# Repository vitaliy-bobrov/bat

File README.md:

# BAT

BAT - custom modified Rat circuit KiCad files.

The repository contains KiCad source files: schematic, PCB, BOM.

## Schematic

## PCB (3D preview)

## Interactive BOM

👉 [BOM](https://vitaliy-bobrov.github.io/bat/)

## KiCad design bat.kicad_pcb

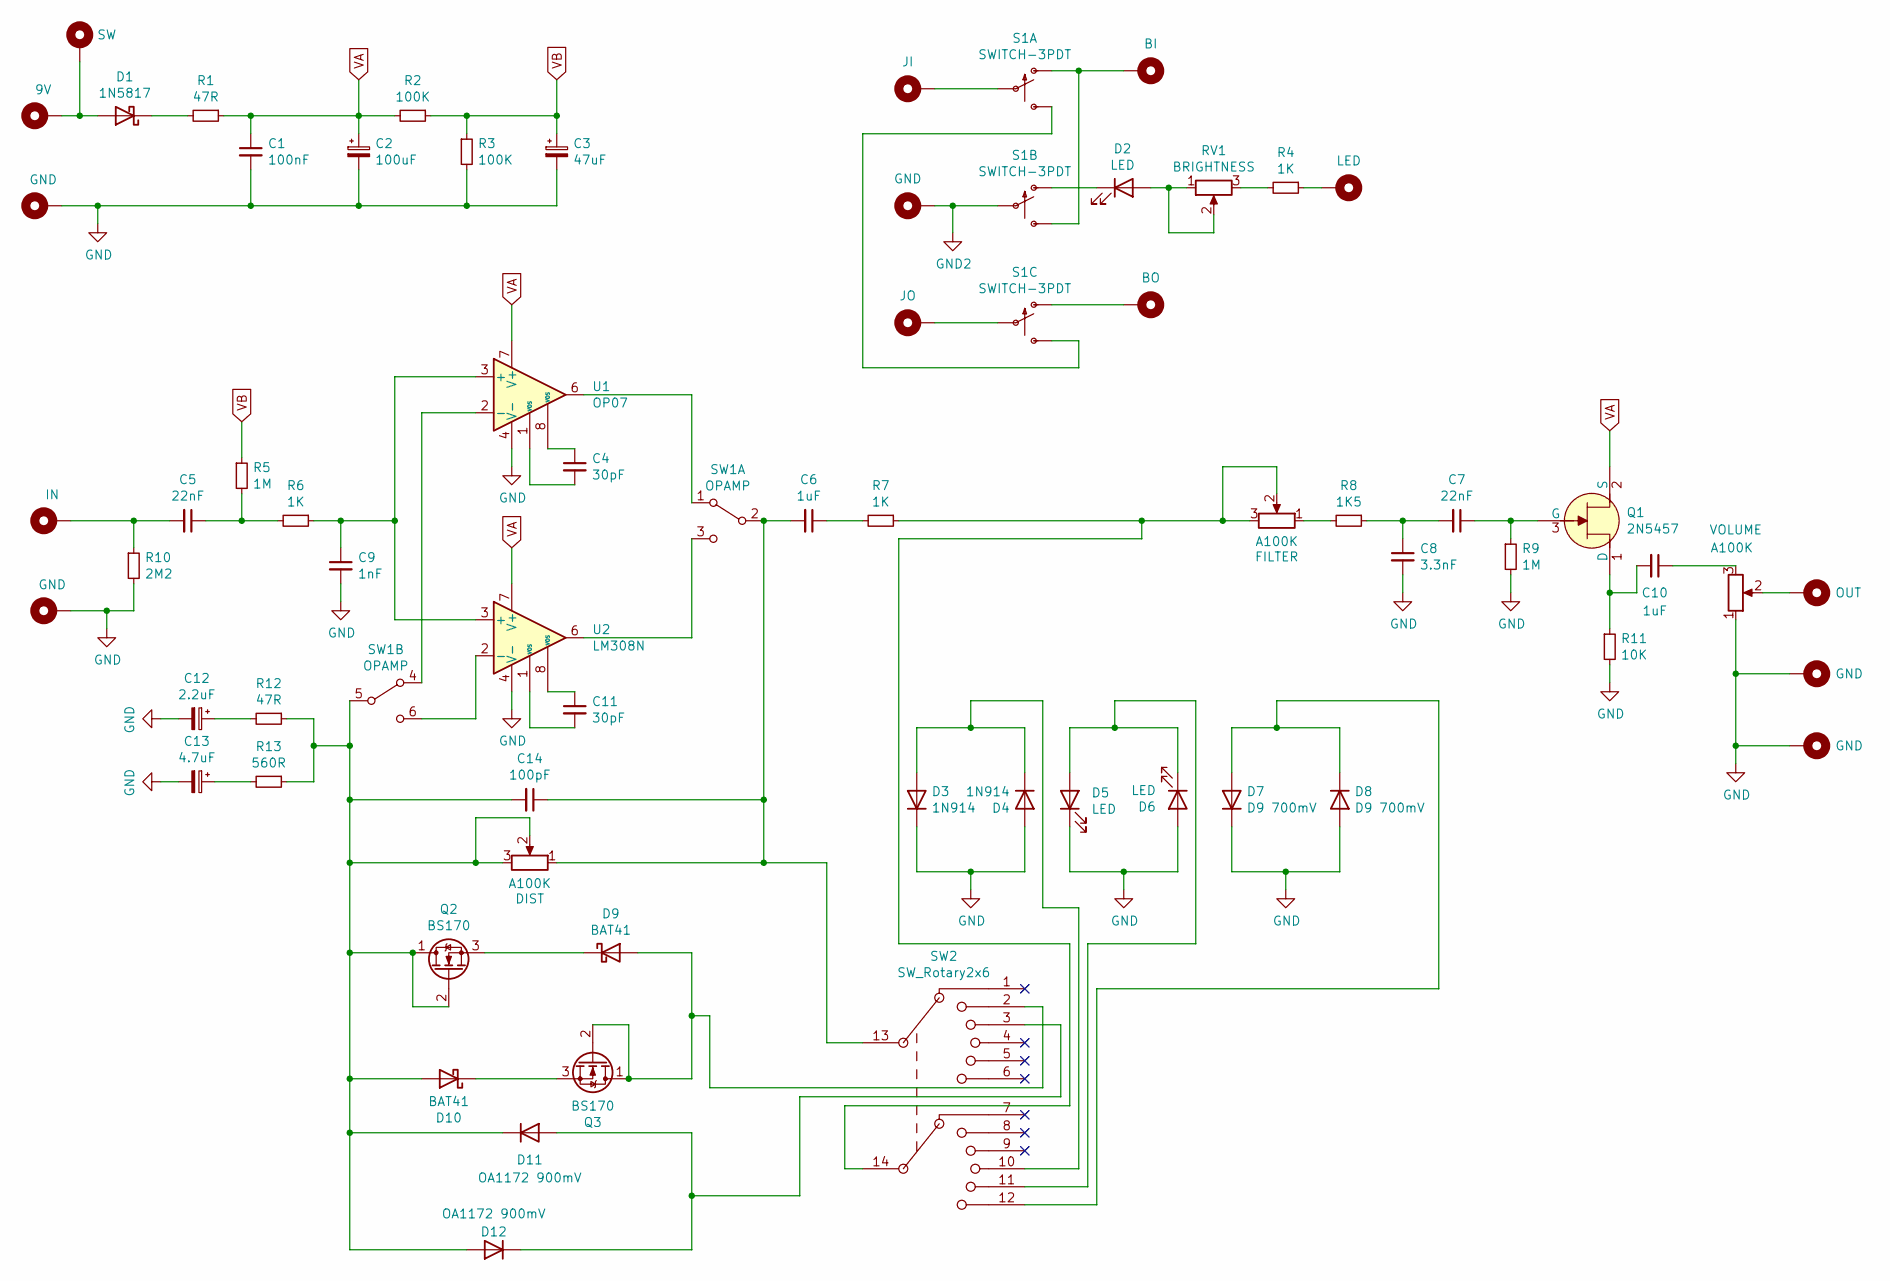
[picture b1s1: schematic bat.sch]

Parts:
C1: 100nF; 0.2_22.SML
C2: 100uF; 0503
C3: 47uF; 0503
C4, C11: 30pF; 0.1%22
C5, C7: 22nF; 0.3%22
C6, C10: 1uF; 0.2_22.LRG
C8: 3.3nF; 0.2_22.SML
C9: 1nF; 0.2_22.SML
C12: 2.2uF; 0502
C13: 4.7uF; 0502
C14: 100pF; 0.2_22.MED
D1: 1N5817; DO41-3
D2: LED; 3MM_IO
D3, D4: 1N914; DO35-3
D5, D6: LED; 3MM_1
D7, D8: D9 700mV; DO35-4
D9, D10: BAT41; DO35-2
D11, D12: OA1172 900mV; DO35-4
H1: SW; PAD3
H2: BI; PAD1
H3: JI; PAD1
H4: 9V; PAD3
H5: LED; PAD1
H6, H7, H16, H17, H18: GND; PAD1
H8: BO; PAD1
H9: JO; PAD1
H10: IN; PAD1
H15: OUT; PAD1
Q1: 2N5457; SOT-23-3
Q2, Q3: BS170; SOT-23-3
R1, R12: 47R; 0.3_22.B
R2, R3: 100K; 0.3_22.B
R4, R6, R7: 1K; 0.3_22.B
R5, R9: 1M; 0.3_22.B
R8: 1K5; 0.3_22.B
R10: 2M2; 0.2%22
R11: 10K; 0.3_22.B
R13: 560R; 0.3_22.B
RV1: BRIGHTNESS; TRIM1
RV2, RV3, RV4: A100K; 16MM_B.MOUNT
S1: SWITCH-3PDT; 3PDT.LUGS.SPF
SW1: OPAMP; DPDT.LUGS
SW2: SW_Rotary2x6; LORINCK1049
U1: OP07; DIP08
U2: LM308N; DIP08

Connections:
GND: C1.2, C2.2, C3.2, C8.2, C9.2, C12.2, C13.2, D3.1 (K), D4.2 (A), D5.1 (K), D6.2 (A), D7.1 (K), D8.2 (A), H6.1, H16.1, H17.1, H18.1, R3.2, R9.2, R10.2, R11.2, RV3.1, U1.4 (V-), U2.4 (V-); also elsewhere on the board
GND2: H7.1, S1.P$5
unnamed 2: C4.1, U1.8 (VOS); also elsewhere on the board
unnamed 3: C4.2, U1.1 (VOS); also elsewhere on the board
unnamed: C5.1, R5.2, R6.2
unnamed: C5.2, H10.1, R10.1
unnamed: C6.1, R7.2
unnamed: C7.1, Q1.3 (G), R9.1
unnamed: C7.2, C8.1, R8.1
unnamed 9: C9.1, R6.1, U1.3 (+), U2.3 (+); also elsewhere on the board
unnamed: C10.1, RV3.3
unnamed: C10.2, Q1.1 (D), R11.1
unnamed 12: C11.1, U2.8 (VOS); also elsewhere on the board
unnamed 13: C11.2, U2.1 (VOS); also elsewhere on the board
unnamed: C12.1, R12.2
unnamed: C13.1, R13.2
unnamed: C6.2, C14.1, RV4.1, SW1.2 (B), SW2.13
unnamed: C14.2, D10.2 (A), D11.1 (K), D12.2 (A), Q2.1 (D), Q2.2 (G), R12.1, R13.1, RV4.2, RV4.3, SW1.5 (B)
unnamed: D1.1 (K), R1.2
unnamed: D1.2 (A), H1.1, H4.1
unnamed: D2.1 (K), S1.P$4 (O)
unnamed: D2.2 (A), RV1.1, RV1.2
unnamed: D3.2 (A), D4.1 (K), SW2.10
unnamed: D5.2 (A), D6.1 (K), SW2.11
unnamed: D7.2 (A), D8.1 (K), SW2.12
unnamed: D9.1 (K), Q2.3 (S)
unnamed: D9.2 (A), Q3.1 (D), Q3.2 (G), SW2.2
unnamed: D10.1 (K), Q3.3 (S)
unnamed: D11.2 (A), D12.1 (K), SW2.3
unnamed: H2.1, S1.P$1 (O), S1.P$6 (S)
unnamed: H3.1, S1.P$2
unnamed: H5.1, R4.1
unnamed: H8.1, S1.P$7 (O)
unnamed: H9.1, S1.P$8
unnamed: H15.1, RV3.2
unnamed: R4.2, RV1.3
unnamed: R7.1, RV2.2, RV2.3, SW2.14
unnamed: R8.2, RV2.1
unnamed: S1.P$3 (S), S1.P$9 (S)
unnamed 39: SW1.1 (A), U1.6; also elsewhere on the board
unnamed 40: SW1.3 (C), U2.6; also elsewhere on the board
unnamed 41: SW1.4 (A), U1.2 (-); also elsewhere on the board
unnamed 42: SW1.6 (C), U2.2 (-); also elsewhere on the board
VA: C1.1, C2.1, Q1.2 (S), R1.1, R2.2, U1.7 (V+), U2.7 (V+); also elsewhere on the board
VB: C3.1, R2.1, R3.1, R5.1

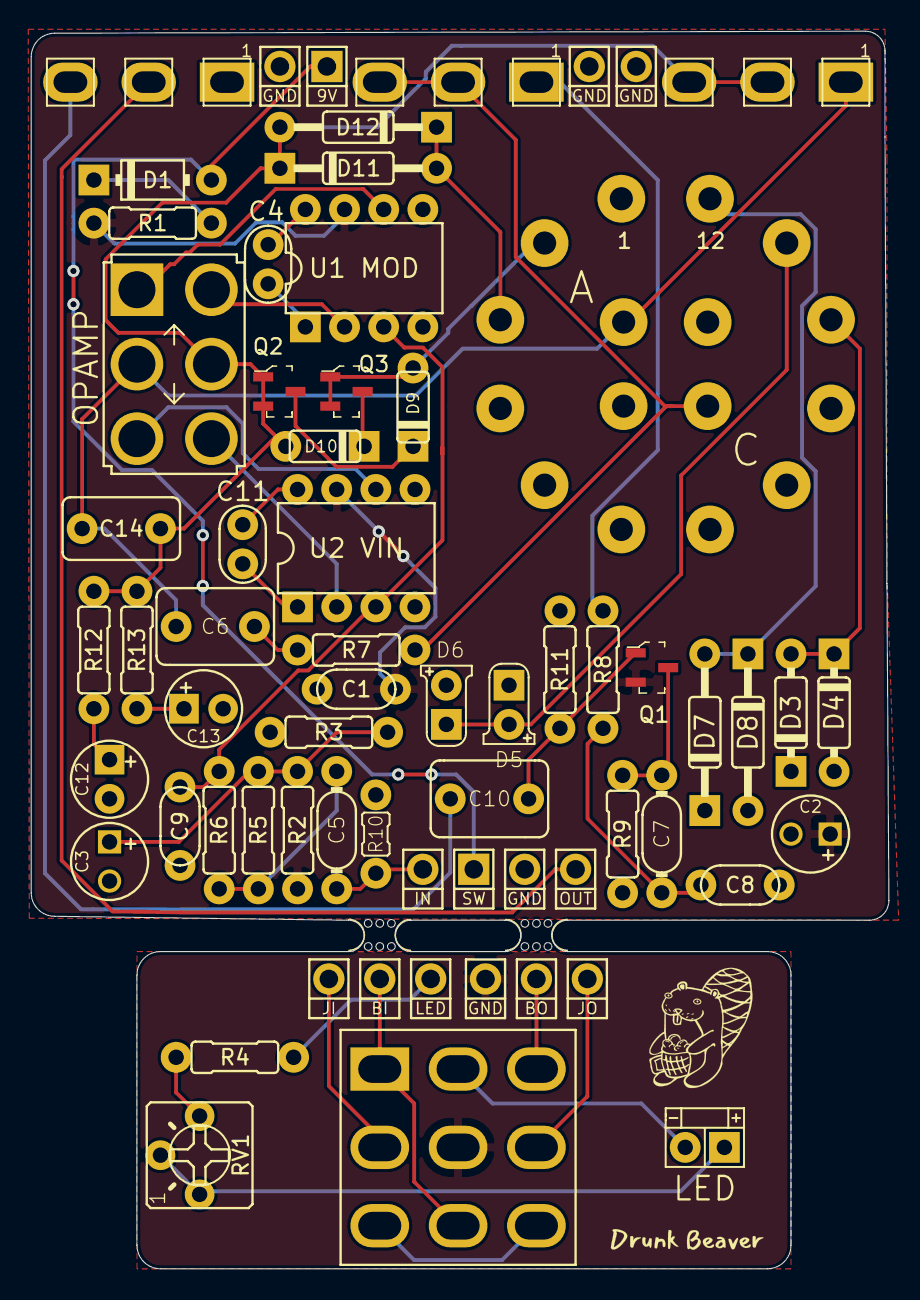
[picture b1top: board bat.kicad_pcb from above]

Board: 2 copper layers, 55.6 x 80.3 mm, 68 parts (1 on the bottom side), 45 nets.

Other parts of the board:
Ref**: Val**; DC_TOP
U1 MOD: OP07; DIP08
U2 VIN: LM308N; DIP08
mouse-bite-2mm-slot, mouse-bite-2mm-slot#2: VAL**; mouse-bite-2mm-slot

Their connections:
GND: U1 MOD.4, U2 VIN.4; also elsewhere on the board
unnamed 2: U1 MOD.8; also elsewhere on the board
unnamed 3: U1 MOD.1; also elsewhere on the board
unnamed 9: U1 MOD.3, U2 VIN.3; also elsewhere on the board
unnamed 12: U2 VIN.8; also elsewhere on the board
unnamed 13: U2 VIN.1; also elsewhere on the board
unnamed 39: U1 MOD.6; also elsewhere on the board
unnamed 40: U2 VIN.6; also elsewhere on the board
unnamed 41: U1 MOD.2; also elsewhere on the board
unnamed 42: U2 VIN.2; also elsewhere on the board
VA: U1 MOD.7, U2 VIN.7; also elsewhere on the board

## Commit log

2021-02-11 v1.0
